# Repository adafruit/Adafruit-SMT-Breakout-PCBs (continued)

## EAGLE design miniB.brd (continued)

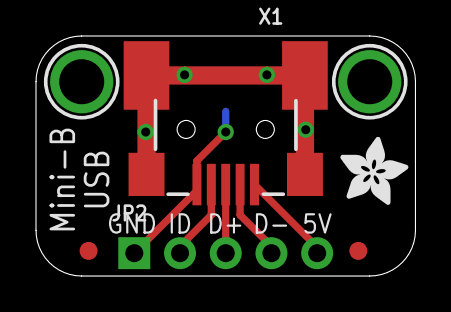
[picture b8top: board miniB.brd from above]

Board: 2 copper layers, 21.1 x 13.3 mm, 7 parts (0 on the bottom side), 5 nets.

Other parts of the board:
U$4: ADAFRUIT_3.5MM

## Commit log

2015-04-28 yeahhhhhhhhhhhhhhhhhhhhh
2015-04-28 read url
2016-08-30 add 20mm coin batts
2016-09-12 PID 334
2021-08-11 Added DVI breakout files
2021-08-11 Added DVI to readme
2026-06-03 update file format to XML
